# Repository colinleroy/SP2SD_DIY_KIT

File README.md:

# Why this fork?

I recently bought an SPIISD v2 kit so that I could have a "hard drive" on my Apple //c.
My use-case is to be able to save documents, photos, programs to a large storage, because
floppies are... small.

Upon testing, I was disappointed to see that the SPIISD v2 works great, in conjunction with
ROM4x, when we boot the Apple //c from Smartport using the ROM4x menu, but that the drive
was "invisible" when booting from the internal floppy disk drive.

I was told this was a limitation of the Apple //c firmware, but could not believe it, as
it was documented nowhere on Internet, and people back in the day would have had a hard time
booting from an external hard disk drive without any means to initialize it.

This is when the second disappointment happened: I wanted to investigate the problem, but when
I bought the SPIISD v2, I missed the part in the documentation that says that the v2 firmware
is closed-source. I doubt the legality of this, given that it seems heavily based on the v1.17
firmware which is MIT-licensed, but that is not my main problem so far, as I so far had no
copyright on v1.17. I was mostly annoyed that I couldn't debug anything further than looking
at serial logs.

I traced the PCB connections from the IDC-20 Smartport connector to the Nano, and the ones
from the SD card module to the Nano, ignored the four buttons and the screen, and compared
those to the gerber files for the v1 board (those are [here](SPSD_DIY_NANO_GERBER)).
All connections matching, I flashed the v1.17 firmware on my v2 board, and started debugging.

So far, this repository fixes my problem: the SPIISD board was booting too slowly, and
missed the first Smartport RESET and ENABLE at cold boot, and so could not advertise its
existence to the Apple //c.

I solved it by reflashing the firmware using an AVR ISP mkII programmer, which bypasses the
Arduino's bootloader. As this was not enough, I defer slow inits to after having replied to the
computer.

# I have an official SPIISD and the same problem, how do I fix it

If you're here because you want your Apple IIc to see your SPIISD (v1 or v2) on cold boot,
here are your options:

- Hit Ctrl-Open-Apple-Reset one second after cold booting. This re-resets the Smartport bus,
but this time the SPIISD is booted.
- Power your SPIISD via an USB adapter, so that it's on before the //c
- Flash this firmware to your board, using a programmer instead of the USB connection, to
fix the root of the problem.

*Warning*: If you flash this firmware on an SPIISD v2 board, you will lose the screen and
buttons functionalities. If you flash this firmware on a v1 board, you will lose the "Eject"
button that is used to switch the SPIISD's bootable image.

In any case, backup your original firmware, using (via USB connection to the nano):
```
avrdude -c arduino -P /dev/ttyUSB0 -b 115200 -p m328p -U flash:r:SPIISD.orig.hex
```

If needed, you can restore it by first using the arduino IDE to reflash the bootloader:
- Tools / Board : Arduino Nano
- Tools / Processor : ATmega328P
- Tools / Programmer: AVR ISP mkII (or whatever your programmer is)
- Tools : Burn bootloader

Then reflash the firmware using your backup:
```
avrdude -c arduino -P /dev/ttyUSB0 -b 115200 -p m328p -U flash:w:SPIISD.orig.hex
```

# Directions for this project

I am not yet sure what I want to do with this project. I would like to have my
firmware conform to my needs (for example, I need only one or two partitions, and
I dislike seeing S2D1 and S2D2 when I won't use them). I would also like it to
be a good, solid Smartport hard drive implementation that would benefit the
community at large: while it is easy to find mass storage solutions for the
slotted Apple IIs, there are far less options to the //c, and as far as I know,
only one - the out-of-stock SPIISD v1 - is open-source.

So, if people are interested in such a project, I'm in. I am bad at hardware,
and while I can wire shit to the correct pins to make prototypes, I have zero
experience at making PCBs and each time I try to learn it's a nightmare. I'm
also bad at 3D printing and couldn't design and print an enclosure. But I'm
quite good at software.

So far, only huge nerds can use this firmware: it requires competency in Arduino
flashing *and* in what to do to transform gerber files into PCBs: the v1 board
is out of stock at Kero Mac Mods store, and the PCB is licensed under the CC-BY-NC-SA,
which prohibits others to step up, have some built and sell them to the community.
(Or, you could by a v2 board and use this firmware. Still, it's not as easy as
it should).

So what I would love to is to design a new PCB, MIT-licensed too, so that anyone
interested could build and sell them. Probably not me, I don't want to turn my
hobby into work.

Then I would like to fix/add features, maybe:
- fix the Eject button so that one can rotate their bootable image
- a jumper block to select 1, 2 or 4 partitions possible
- a clean-room implementation of a basic image selection UI

# SPIISD DIY KIT

<br>

# What is SPIISD ?
It is based on an open source project called SmartPortSD. 
Created by Australian genius [Robert Justice](https://web.archive.org/web/20230222233834/http://www.users.on.net/~rjustice/SmartportCFA/SmartportCFA.htm), SmartPortCFA was ported to Arduino hardware by Italian programmer genius [Andrea Ottaviani](https://github.com/aotta?fbclid=IwAR0_7cMKVhMVrHznB9bIub9ZmrmBlwAM3p6-_CQd0JFW1o736nUNZHyuTdw).  to porting to Arduino hardware. It was improved upon by [Katherine Stark](https://gitlab.com/nyankat/smartportsd) of Canada. She made available its ability to access four ProDOS-formatted 32MB PO files stored on a FAT32-formatted SD card. When she did this successfully, many wanted to build it.

*Got permission from the three geniuses I introduced earlier.<BR><BR>

We differentiated it with a name to distinguish it from other SmartportSD hardware (including unlicensed ones).<BR><BR>

<BR>
More details here (My Blog):
https://ameblo.jp/keroxiee1016/entry-12819341808.html

## Flashing Arduino Nano

Oct 15th, 2024: SmartportSD program has been updated to Ver.1.17, version 1.17 has been thoroughly tested with "SPIISD" hardware and has confirmed good performance. Fixed a problem with the Apple IIcPlus, and improved versatility with slower SD cards. Usage is the same as V.1.16.

May 8th, 2024: SmartportSD program has been updated to Ver.1.16 by Wing Yeung from [MFA2 work shop](http://www.mfa2lab.com). version 1.16 has been thoroughly tested with "SPIISD" hardware and has confirmed good performance. This same 1.16 program can work with both "SPIISD DIY KIT" and "SPIISD MINI". *We have not verified SmartportSD compatible devices from other manufacturers. I think they work well if they keep the same schematics.<BR>

- By placing "config.txt" at the root of the SD card, you can place various files without renaming them.<BR>
- Write 4x file names in "config.txt". SPIISD will only read files with that filename.
In addition to ".po", ".hdv" and ".2mg" can be used as extensions.<BR>
- Of course, you can put an unlimited number of images in the root of the SD card, but only the config.txt file will be read.<BR>
- If you do not place config.txt, you can also place four files from PART1.po as before.<BR>

You can flash your Arduino Nano via ArduinoIDE. Please download and use firmware of ["SmartportSD-1.17" folder](SmartportSD-1.17). If a new folder is created when using the Arduino IDE, please re-insert all the contents of this "SmartportSD-1.17" folder into the new folder. *The name of the ".ino" file should always be the same as the parent folder, so there is usually no problem if you use it as is.<BR>
<BR>
The Nano board you should choose is MEGA328P. Please do not buy MEGA168P as it has 38% insufficient capacity and cannot be flashed.<BR>
<BR>
The Arduino IDE settings are as follows,<BR>
Board: "Arduino Nano"<BR>
Processor: "ATmega328P(Old Bootloader)"<BR>
Port: Number of USB port connected to Arduino Nano *In your PC<BR>
Programmer: "AVRISP mkII"<BR>

## Assemble
Uploaded on Sep 24, assembly instructions can be found [here](SP2SD_DIY_INST.pdf), You can see which parts should be attached where by looking at our [BOM](SP2SD_NANO_DIY_BOM.csv). 
<BR>

<BR>
The IDC20 connector can be oriented in various ways depending on how you use it, When installing the male IDC20pin connector, be sure to make sure that the part is on the top side. When stacking two PCBs, make sure the hole and ▼ are in the same position. In that case, match the IDC20pin male and female connectors or connect them with a 2X10 pin header.<BR><BR>
日本語の組み立て説明書は[こちら](SP2SD_DIY_INST_JPN.pdf)から

## DB19 male connector

You can 3D print the base material and pull out the pins from a [DB25 male connector](https://www.amazon.com/PC-Accessories-Connectors-Connector-25-PACK/dp/B073KR622F/ref=sr_1_2_sspa?crid=2ZCRZ8PNIBJ4R&keywords=DB25+connector+male&qid=1693987417&sprefix=db25+connector+mal%2Caps%2C398&sr=8-2-spons&sp_csd=d2lkZ2V0TmFtZT1zcF9hdGY&psc=1) and insert them, or purchase new pins from [AliExpress](https://www.aliexpress.com/item/1005002617586407.html?spm=a2g0o.order_list.order_list_main.16.55d11802jCHaOW). We have omitted unnecessary pins to make it simple for you to create. I will give out free .STL files that can be 3D printed. <BR><BR> DB19 connector file is [this](KEROS_DB19_V1.zip).

## 3D printed shell case

Our awesome friend [Mr Lurch](https://www.youtube.com/channel/UCMQ28v823w6p1ZnyiZDVwUg) completed the shell case design. This can be used by connecting boards A and B with pin headers without using cables.<BR><BR>
 [Here](https://www.thingiverse.com/thing:6235981) is the case stl files for integrated.<BR>
 [Here](https://www.thingiverse.com/thing:6248598) is the case stl files for cable connection.

## Supported Apple II computers

<BR>

<BR><BR>
- Apple IIgs　*Even you set the startup slot to #5 and remove other bootable devices the startup timing does not match, try the shortcut key "Open Apple" + "Control" + "Reset" to reboot. If you are new to IIgs, make sure to release key "Open Apple"　 last and it will reboot easily.<BR>
- Apple IIc, IIc Plus *In the case of IIc, Smartport cannot be used as is with older ROM 255, so a ROM upgrade is required. See the chapter bellow
- Apple IIe, IIe Enhanced, IIe Platinum, works well with Grappler Minus card (1) with SoftSP diy ROM V2, V3 and V6-a. It works into the #5 slot and use it via the DiskII card in the #6 slot. In other words, it is a card that connects SmartPort with two cards.<BR>*You can also use it via "Liron" card, BMOW also has a highly functional card called "Yellowstone", which can also be used. <BR>
- Apple II Plus, works well with GrapplerMinus card with SoftSP diy ROM V2, V3 and V6-a.<BR>

(1) We developed the [Grappler Minus card](https://github.com/kerokero5150/GrapplerMinus/blob/main/README.md), which overcomes timing issues. This is also open source and anyone can create it, but it is not allowed to be sold. It is also available for purchase at our store. <BR><BR>
If you use SoftSP with the Genuine "Grappler Plus" card, the functionality of SoftSP DIY will be limited due to the unnecessary circuitry of the printer interface. Specifically, it only works with Apple IIe, and only V2 and V3 ROMs can be used.

## Usage
<BR>
Use a FAT32(16) formatted MicroSD card. Most of the MicroSD cards currently on sale can be used as is.
Extension .po files can be used.<BR><BR>

### Usage V.1.17(1.16)
New firmware allows the use of three file extensions: ".po", ".hdv", ".2mg", each files with a maximum size of 32MB.
As we have upgraded to V.1.17(1.16), the new method for setting up the SD card is described below. From v1.16 onwards, if "config.txt" is not placed in the root, it will be automatically recognized and converted to the old method. Please refer to “2, Old method” when "config.txt" is not placed.＜BR>
Place "config.txt" in the root of the SD card, this is a standard text document, which can be created using any text editors. This is the table of contents for loading the specified file into the Apple II. The contents of "config.txt" must have a file name written on each line, and you can specify up to four files to launch. You can add as many files as you like up to the capacity of the SD card. However, SPIISD can only read the four files with the names written in config.txt. The file extensions are either ".po", ".hdv", or ".2mg". SPIISD will read from the first file written (on the first line). Please keep in mind that the file specification must always be 4 lines for 4files.

### Usage up to V.1.15<BR>
The Apple ProDOS disk image that can be used for SPIISD is a .PO file with a maximum size of 32MB. Place this file at the root of your micro SD card. Up to 4 files can be recognized. The first file name should be “PART1.PO”. As you can imagine, there can place four files, so from the second file on, name the files with regularity, such as "PART2.PO", "PART3.PO", and "PART4.PO".<BR>
For disk images with the .hdv extension, the catalog structure is the same, so you should be able to use them by simply renaming the file to .po. An APP called CiderPressV4 can convert other file extensions to .po.<BR><BR>
I think the most popular way to use SPIISD on the IIc is to use TotalReplay, a collection of old appleII games. <BR>
The IIgs supports GSOS. In this case, you can check all four files at the same time on the OS's finder. If you only have a IIgs, the SPIISD is the device with the best value for money.<BR><BR>
*If you change the extension from .hdv to .po and it doesn't work, you can use CiderPress to convert it to a .PO file. CiderPressV4 can be done on Windows 7 and up. *For Win98/ME/2K/XP there is an older version.<BR>
<BR>
CiderPress V4:<BR>(https://a2ciderpress.com)<BR><BR>
TotalReplay:<BR>(https://archive.org/details/TotalReplay)<BR><BR>

## To use Apple IIc's smart port
For Apple IIc, Smartport will not be enabled if ROM 255 is installed(Probably ROM0 as well). To check the ROM of your IIc, run the following program from the Basic prompt.
  PRINT PEEK (64447)
If the output number is "255", the ROM needs to be replaced. The ROM versions that Smartport can use are "3", "4" and ROM"4x". For these numbers, ROM replacement is not necessary.

The replaced ROMs are available [here](https://mirrors.apple2.org.za/Apple%20II%20Documentation%20Project/Computers/Apple%20II/Apple%20IIc/ROM%20Images/).
There is also the useful hacked [ROM4X](https://github.com/mgcaret/rom4x). This is a fairly new ROM updated in 2018.<BR><BR>

My recommendation is ROM4X.<BR>

If you want to swap the ROM from 255 to another ROM, you need to change the solder jumpers "W1" and "W2". 
255 is 16KB while other ROMs are 32KB. Enable 32KB by changing Pin27, which is A14, from pull-down to pull-up. 
See below for solder jumper locations. [External site](https://www.apple2faq.com/apple2faq/apple-iic-rom-upgrade/?fbclid=IwAR3BZfkTRkhG0zg6dHxvxYdH9SbyCvsA-Zr1-_e0wyenW6WFG-cKSsxj_oM)

## To get the SPIISD PCB

You can use [SPSD_DIY_NANO_GERBER.zip](SPSD_DIY_NANO_GERBER.zip)  and uploading it to JLCPCB or PCBWAY as it is.

<BR>

The [SPIISD DIY kit](https://en.infinityproducts.co.jp/product-page/sp2sd-diykit-bare-pcb-board-a-b) comes complete with all parts, sold in our [store](https://en.infinityproducts.co.jp/shop-1). [SPIISD mini](https://en.infinityproducts.co.jp/product-page/spiisd-mini-for-iic-iicplus-iigs) is a compact hardware with fixed db19. It does not require assembly, so it is recommended for those who want to use it immediately, and for those who want a sense of unity with Apple IIc.

## Licenses

SmartportSD software licenses are listed [here](SMARTPORTSD_LICENSE.md) under the MIT license.
Ⓒ2023 Katherine Stark, Robert Justice, Andrea Ottaviani. All rights reserved.

This SPIISD hardware is licensed under a
[Creative Commons Attribution-ShareAlike 4.0 International License](https://creativecommons.org/licenses/by-nc-sa/4.0/).
Ⓒ 2023 Kay Koba, Kero's mac Mods, All rights reserved.

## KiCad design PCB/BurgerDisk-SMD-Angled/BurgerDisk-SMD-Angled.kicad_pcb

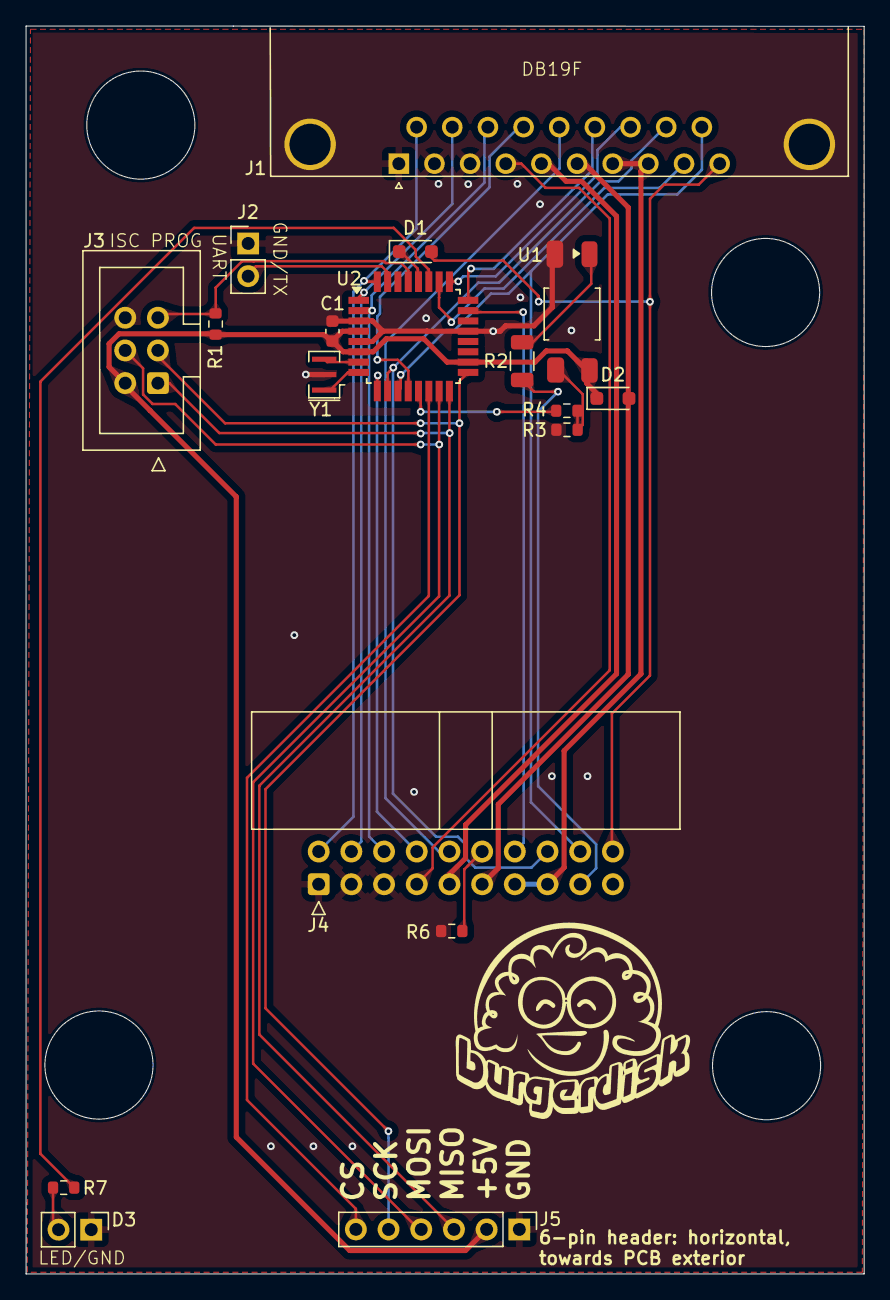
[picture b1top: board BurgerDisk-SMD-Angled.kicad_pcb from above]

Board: 2 copper layers, 65.1 x 96.9 mm, 18 parts (0 on the bottom side), 35 nets.

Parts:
C1: 100n; C_0603_1608Metric
D1: 1N4448WS; D_SOD-323_HandSoldering
D2: 1N5818WS; D_SOD-323_HandSoldering
D3: LED; PinHeader_1x02_P2.54mm_Vertical
J1: Daisy port out; DSUB-19_Female_Horizontal_MXS82009-8251-9246
J2: 2-pin header; PinHeader_1x02_P2.54mm_Vertical
J3: ICSP_ISP6; IDC-Header_2x03_P2.54mm_Vertical
J4: Daisy port in; IDC-Header_2x10_P2.54mm_Horizontal
J5: MicroSD module; PinHeader_1x06_P2.54mm_Vertical
R1: 10K; R_0603_1608Metric
R2: 470; R_1206_3216Metric
R3: 10k; R_0603_1608Metric
R4: 1k; R_0603_1608Metric
R6: 330; R_0603_1608Metric
R7: 150; R_0603_1608Metric
U1: PC817C-S; SOP-4_3.8x4.1mm_P2.54mm
U2: ATmega328P-AU; TQFP-32_7x7mm_P0.8mm
Y1: Resonator_GND2; Resonator_SMD_Murata_CSTxExxV-3Pin_3.0x1.1mm

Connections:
5V_apple2: D2.2 (A), J1.6, J4.11
5V_burgerDisk: C1.1, D2.1 (K), J3.2, J5.2, R1.1, U1.4, U2.4 (VCC), U2.6 (VCC), U2.18 (AVCC)
+12V: J1.7, J1.8, J4.13, J4.15
-12V: J1.5, J4.9
CS: J5.6, U2.14 (PB2)
DRV1_in: J4.14, U2.23 (PC0)
DRV1_out: J1.17, U2.25 (PC2)
DRV2_burgerDisk: R4.1, U2.13 (PB1)
DRV2_in: J4.17, R2.1
DRV2_out: J1.9, U2.26 (PC3)
EN3.5: J1.4, J4.7
GND: C1.2, D3.1 (K), J1.0 (GND), J1.1, J1.2, J1.3, J2.1, J3.6, J4.1, J4.3, J4.5, J5.1, R3.1, R6.1, U1.2, U2.3 (GND), U2.5 (GND), U2.21 (GND), Y1.2
HDSEL_in: J4.12, R6.2
HDSEL_out: J1.16, U2.24 (PC1)
LED: R7.2, U2.27 (PC4)
MISO: J3.1, J5.3, U2.16 (PB4)
MOSI: J3.4, J5.4, U2.15 (PB3)
unnamed: D3.2 (A), R7.1
unnamed: R2.2, U1.1
unnamed: R3.2, R4.2, U1.3
unnamed: U2.7 (XTAL1/PB6), Y1.3
unnamed: U2.8 (XTAL2/PB7), Y1.1
PH0: J1.11, J4.2, U2.32 (PD2)
PH1: J1.12, J4.4, U2.1 (PD3)
PH2: J1.13, J4.6, U2.2 (PD4)
PH3_in: J4.8, U2.9 (PD5)
PH3_out: J1.14, U2.12 (PB0)
RDDATA: J1.18, J4.16, U2.10 (PD6)
RESET: J3.5, R1.2, U2.29 (~RESET/PC6)
SCK: J3.3, J5.5, U2.17 (PB5)
TX: J2.2, U2.31 (PD1)
WRDATA: J1.19, J4.18, U2.11 (PD7)
WREQ: J1.15, J4.10
WRPROT_in: D1.1 (K), U2.28 (PC5)
WRPROT_out: D1.2 (A), J1.10, J4.20

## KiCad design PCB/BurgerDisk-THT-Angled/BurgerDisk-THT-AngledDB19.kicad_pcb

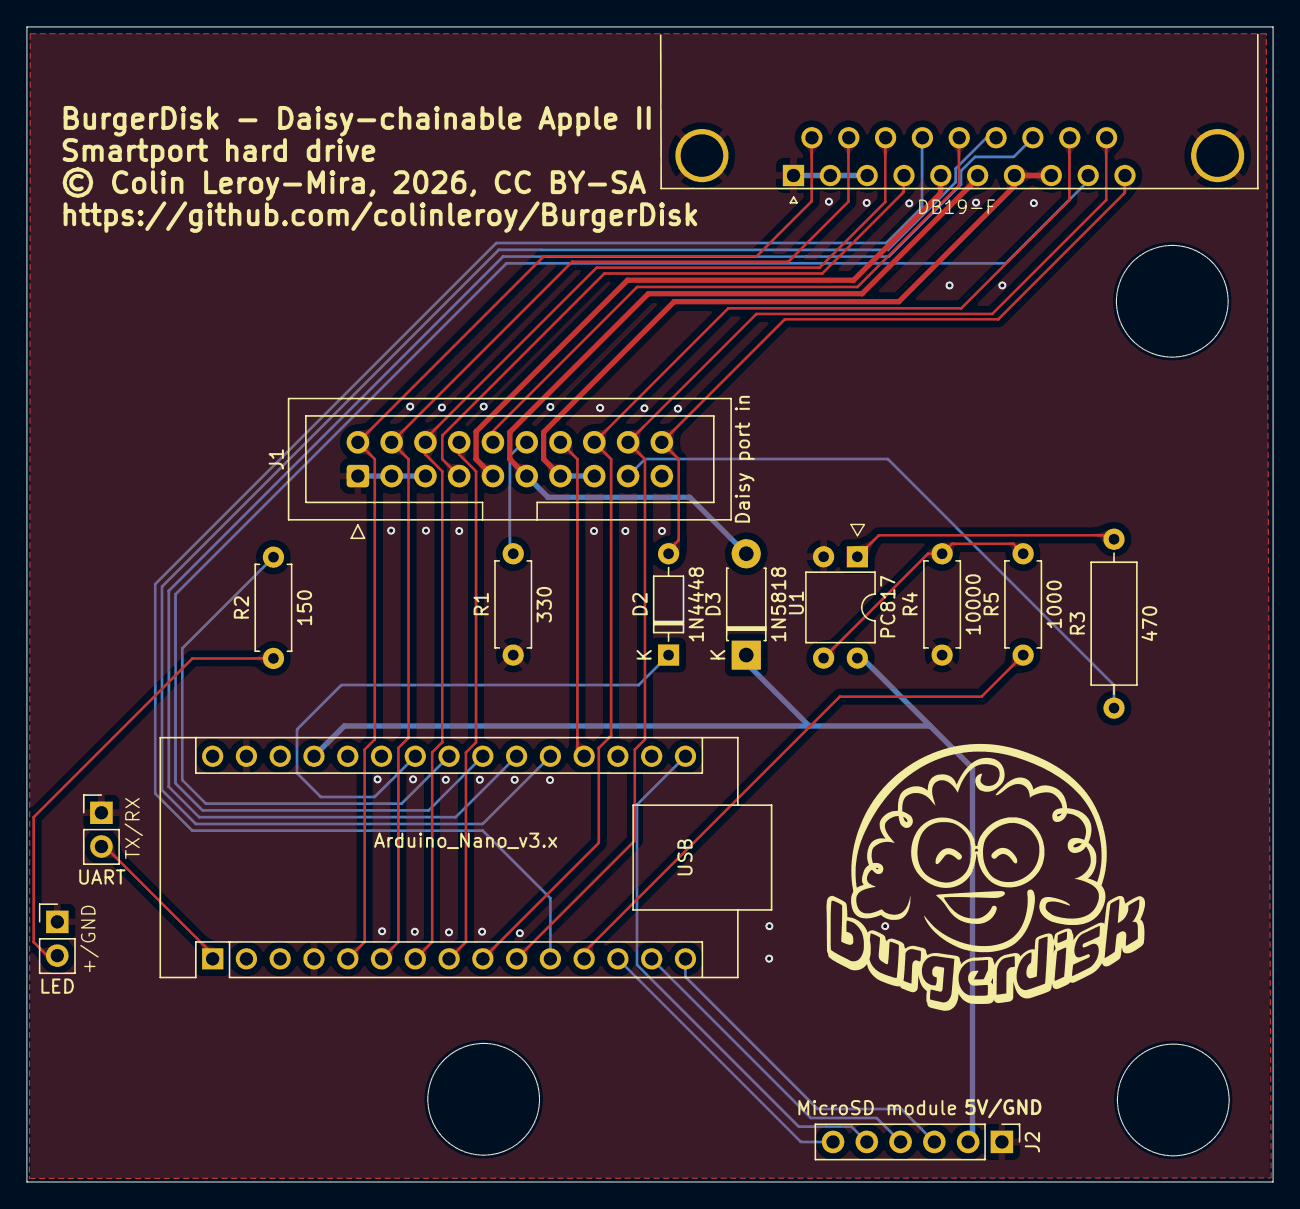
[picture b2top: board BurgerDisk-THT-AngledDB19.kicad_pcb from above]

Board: 2 copper layers, 93.7 x 86.9 mm, 14 parts (0 on the bottom side), 32 nets.

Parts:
A1: Arduino_Nano_v3.x; Arduino_Nano
D2: 1N4448; D_DO-35_SOD27_P7.62mm_Horizontal
D3: 1N5818; D_DO-41_SOD81_P7.62mm_Horizontal
D4: LED; PinHeader_1x02_P2.54mm_Vertical
J1: Daisy port in; IDC-Header_2x10_P2.54mm_Vertical
J2: MicroSD module; PinHeader_1x06_P2.54mm_Vertical
J3: UART; PinHeader_1x02_P2.54mm_Vertical
J4: Daisy port out; DSUB-19_Female_Horizontal_MXS82009-8251-9246
R1: 330; R_Axial_DIN0207_L6.3mm_D2.5mm_P7.62mm_Horizontal
R2: 150; R_Axial_DIN0207_L6.3mm_D2.5mm_P7.62mm_Horizontal
R3: 470; R_Axial_DIN0309_L9.0mm_D3.2mm_P12.70mm_Horizontal
R4: 10000; R_Axial_DIN0207_L6.3mm_D2.5mm_P7.62mm_Horizontal
R5: 1000; R_Axial_DIN0207_L6.3mm_D2.5mm_P7.62mm_Horizontal
U1: PC817; DIP-4_W7.62mm

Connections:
5V_apple2: D3.2 (A), J1.11, J4.6
5V_burgerDisk: A1.27 (+5V), D3.1 (K), J2.2, U1.4
+12V: J1.13, J1.15, J4.7, J4.8
-12V: J1.9, J4.5
CS: A1.13 (D10), J2.6
DRV1_in: A1.19 (A0), J1.14
DRV1_out: A1.21 (A2), J4.17
DRV2_burgerDisk: A1.12 (D9), R5.1
DRV2_in: J1.17, R3.1
DRV2_out: A1.22 (A3), J4.9
EN3.5: J1.7, J4.4
GND: A1.4 (GND), A1.29 (GND), D4.1 (K), J1.1, J1.3, J1.5, J2.1, J3.1, J4.0, J4.1, J4.2, J4.3, R1.1, R4.1, U1.2
HDSEL_in: J1.12, R1.2
HDSEL_out: A1.20 (A1), J4.16
MISO: A1.15 (D12), J2.3
MOSI: A1.14 (D11), J2.4
unnamed: A1.23 (A4), R2.2
unnamed: D4.2 (A), R2.1
unnamed: R3.2, U1.1
unnamed: R4.2, R5.2, U1.3
PH0: A1.5 (D2), J1.2, J4.11
PH1: A1.6 (D3), J1.4, J4.12
PH2: A1.7 (D4), J1.6, J4.13
PH3_in: A1.8 (D5), J1.8
PH3_out: A1.11 (D8), J4.14
RDDATA_in: A1.9 (D6), J1.16, J4.18
SCK: A1.16 (D13), J2.5
TX: A1.1 (D1/TX), J3.2
WRDATA: A1.10 (D7), J1.18, J4.19
WREQ: J1.10, J4.15
WRPROT_in: A1.24 (A5), D2.1 (K)
WRPROT_out: D2.2 (A), J1.20, J4.10

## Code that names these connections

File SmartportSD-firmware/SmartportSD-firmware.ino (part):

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//
// Apple disk interface is connected as follows:
// wrprot = pa5 (ack) (output)
// ph0    = pd2 (req) (input)
// ph1    = pd3       (input)
// ph2    = pd4       (input)
// ph3    = pd5       (input)
// rddata = pd6       (output from avr)
// wrdata = pd7       (input to avr)
//
//led i/o = pa4  (for led on when i/o on boxed version)
//eject button = pa3  (for boxed version, cycle between boot partitions)
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    switch (phases) {

      // phase lines for smartport bus reset
      // ph3=0 ph2=1 ph1=0 ph0=1

      case 0b00000101:
        LOG(F("SP BUS RESET"));
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        break;

      // phase lines for smartport bus enable
      // ph3=1 ph2=x ph1=1 ph0=x
      case 0b00001010:
      case 0b00001011:
      case 0b00001110:
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
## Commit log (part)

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2025-11-18 Create working version
2025-11-18 Whitespace
2025-11-18 More cleanup, add timings in logs
    Makes clear that we have to be in loop() in less than 173ms.
2025-11-18 Update READMEs

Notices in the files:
PCB/BurgerDisk-SMD-Angled/BurgerDisk-SMD-Angled.kicad_pcb:
BurgerDisk - CC BY-SA
© Colin Leroy-Mira 2026
PCB/BurgerDisk-THT-Angled/BurgerDisk-THT-AngledDB19.kicad_pcb:
© Colin Leroy-Mira, 2026, CC BY-SA
README.md:
License: CC BY-NC-SA 4.0
